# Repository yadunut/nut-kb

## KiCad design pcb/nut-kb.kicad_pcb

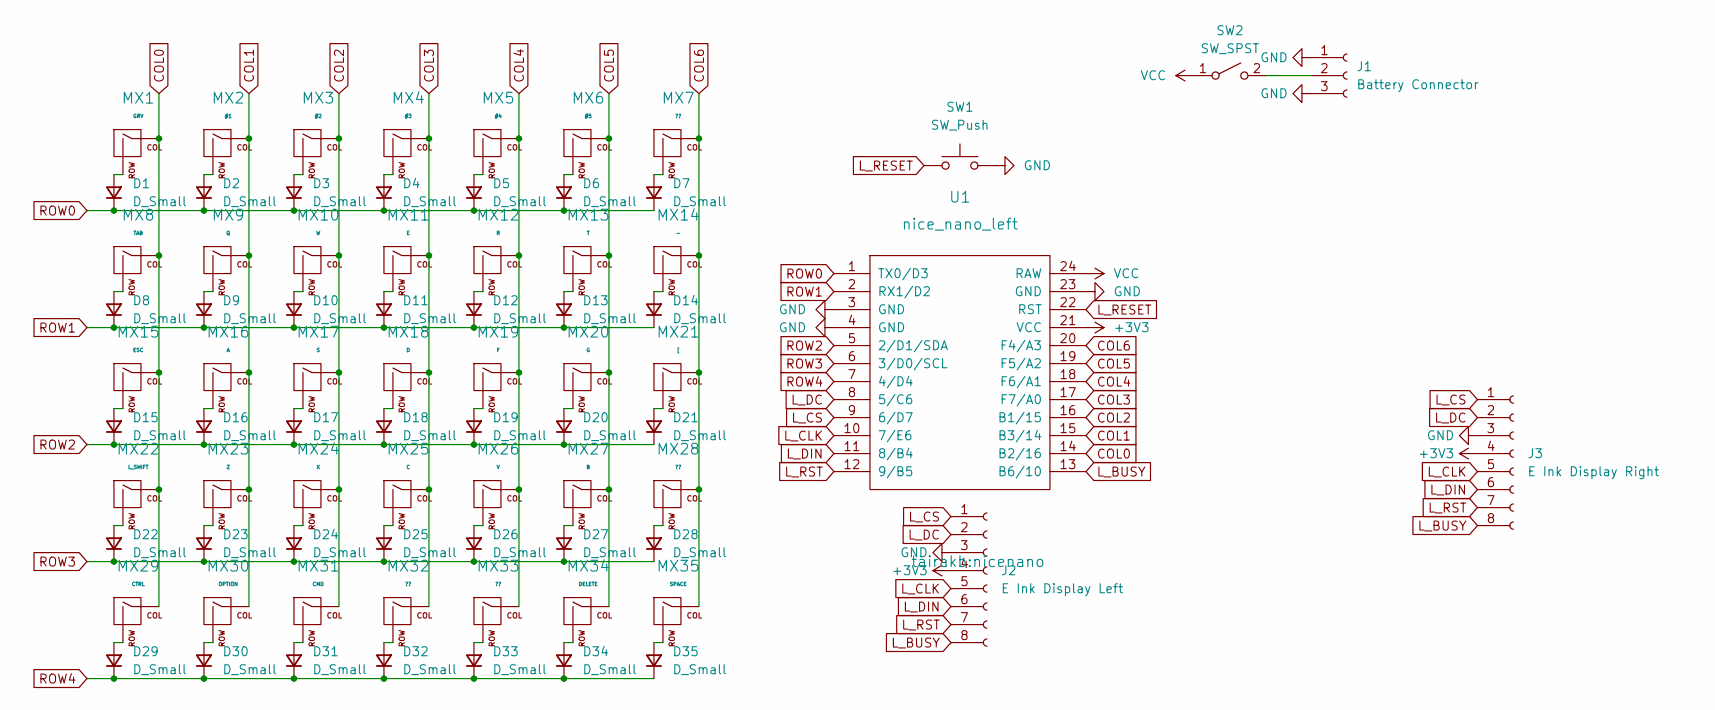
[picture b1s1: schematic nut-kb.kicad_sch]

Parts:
D1, D2, D3, D4, D5, D6, D7, D8, D9, D10, D11, D12, D13, D14, D15, D16, D17, D18, D19, D20, D21, D22, D23, D24, D25, D26, D27, D28, D29, D30, D31, D32, D33, D34, D35: D_Small; D_SOD-123
J1: Battery Connector; JST_PH_B3B-PH-K_1x03_P2.00mm_Vertical
J2: E Ink Display Left; PinSocket_1x08_P2.54mm_Vertical
J3: E Ink Display Right; PinSocket_1x08_P2.54mm_Vertical
MX1: GRV; SW_PG1350_reversible
MX2: #1; SW_PG1350_reversible
MX3: #2; SW_PG1350_reversible
MX4: #3; SW_PG1350_reversible
MX5: #4; SW_PG1350_reversible
MX6: #5; SW_PG1350_reversible
MX7, MX28, MX32, MX33: ??; SW_PG1350_reversible
MX8: TAB; SW_PG1350_reversible
MX9: Q; SW_PG1350_reversible
MX10: W; SW_PG1350_reversible
MX11: E; SW_PG1350_reversible
MX12: R; SW_PG1350_reversible
MX13: T; SW_PG1350_reversible
MX14: -; SW_PG1350_reversible
MX15: ESC; SW_PG1350_reversible
MX16: A; SW_PG1350_reversible
MX17: S; SW_PG1350_reversible
MX18: D; SW_PG1350_reversible
MX19: F; SW_PG1350_reversible
MX20: G; SW_PG1350_reversible
MX21: [; SW_PG1350_reversible
MX22: L_SHIFT; SW_PG1350_reversible
MX23: Z; SW_PG1350_reversible
MX24: X; SW_PG1350_reversible
MX25: C; SW_PG1350_reversible
MX26: V; SW_PG1350_reversible
MX27: B; SW_PG1350_reversible
MX29: CTRL; SW_PG1350_reversible
MX30: OPTION; SW_PG1350_reversible
MX31: CMD; SW_PG1350_reversible
MX34: DELETE; SW_PG1350_reversible
MX35: SPACE; SW_PG1350_reversible
SW1: SW_Push; SW_PUSH_6mm
SW2: SW_SPST; SW_DIP_SPSTx01_Slide_6.7x4.1mm_W7.62mm_P2.54mm_LowProfile
U1: nice_nano_left; nicenano

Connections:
+3V3: J2.4, J3.4, U1.21 (VCC)
COL0: MX1.1 (COL), MX8.1 (COL), MX15.1 (COL), MX22.1 (COL), MX29.1 (COL), U1.14 (B2/16)
COL1: MX2.1 (COL), MX9.1 (COL), MX16.1 (COL), MX23.1 (COL), MX30.1 (COL), U1.15 (B3/14)
COL2: MX3.1 (COL), MX10.1 (COL), MX17.1 (COL), MX24.1 (COL), MX31.1 (COL), U1.16 (B1/15)
COL3: MX4.1 (COL), MX11.1 (COL), MX18.1 (COL), MX25.1 (COL), MX32.1 (COL), U1.17 (F7/A0)
COL4: MX5.1 (COL), MX12.1 (COL), MX19.1 (COL), MX26.1 (COL), MX33.1 (COL), U1.18 (F6/A1)
COL5: MX6.1 (COL), MX13.1 (COL), MX20.1 (COL), MX27.1 (COL), MX34.1 (COL), U1.19 (F5/A2)
COL6: MX7.1 (COL), MX14.1 (COL), MX21.1 (COL), MX28.1 (COL), MX35.1 (COL), U1.20 (F4/A3)
GND: J1.1, J1.3, J2.3, J3.3, SW1.2, U1.3 (GND), U1.4 (GND), U1.23 (GND)
L_BUSY: J2.8, J3.8, U1.13 (B6/10)
L_CLK: J2.5, J3.5, U1.10 (7/E6)
L_CS: J2.1 (asdf), J3.1 (asdf), U1.9 (6/D7)
L_DC: J2.2, J3.2, U1.8 (5/C6)
L_DIN: J2.6, J3.6, U1.11 (8/B4)
L_RESET: SW1.1, U1.22 (RST)
L_RST: J2.7, J3.7, U1.12 (9/B5)
unnamed: D1.2 (A), MX1.2 (ROW)
unnamed: D2.2 (A), MX2.2 (ROW)
unnamed: D3.2 (A), MX3.2 (ROW)
unnamed: D4.2 (A), MX4.2 (ROW)
unnamed: D5.2 (A), MX5.2 (ROW)
unnamed: D6.2 (A), MX6.2 (ROW)
unnamed: D7.2 (A), MX7.2 (ROW)
unnamed: D8.2 (A), MX8.2 (ROW)
unnamed: D9.2 (A), MX9.2 (ROW)
unnamed: D10.2 (A), MX10.2 (ROW)
unnamed: D11.2 (A), MX11.2 (ROW)
unnamed: D12.2 (A), MX12.2 (ROW)
unnamed: D13.2 (A), MX13.2 (ROW)
unnamed: D14.2 (A), MX14.2 (ROW)
unnamed: D15.2 (A), MX15.2 (ROW)
unnamed: D16.2 (A), MX16.2 (ROW)
unnamed: D17.2 (A), MX17.2 (ROW)
unnamed: D18.2 (A), MX18.2 (ROW)
unnamed: D19.2 (A), MX19.2 (ROW)
unnamed: D20.2 (A), MX20.2 (ROW)
unnamed: D21.2 (A), MX21.2 (ROW)
unnamed: D22.2 (A), MX22.2 (ROW)
unnamed: D23.2 (A), MX23.2 (ROW)
unnamed: D24.2 (A), MX24.2 (ROW)
unnamed: D25.2 (A), MX25.2 (ROW)
unnamed: D26.2 (A), MX26.2 (ROW)
unnamed: D27.2 (A), MX27.2 (ROW)
unnamed: D28.2 (A), MX28.2 (ROW)
unnamed: D29.2 (A), MX29.2 (ROW)
unnamed: D30.2 (A), MX30.2 (ROW)
unnamed: D31.2 (A), MX31.2 (ROW)
unnamed: D32.2 (A), MX32.2 (ROW)
unnamed: D33.2 (A), MX33.2 (ROW)
unnamed: D34.2 (A), MX34.2 (ROW)
unnamed: D35.2 (A), MX35.2 (ROW)
unnamed: J1.2, SW2.2 (B)
ROW0: D1.1 (K), D2.1 (K), D3.1 (K), D4.1 (K), D5.1 (K), D6.1 (K), D7.1 (K), U1.1 (TX0/D3)
ROW1: D8.1 (K), D9.1 (K), D10.1 (K), D11.1 (K), D12.1 (K), D13.1 (K), D14.1 (K), U1.2 (RX1/D2)
ROW2: D15.1 (K), D16.1 (K), D17.1 (K), D18.1 (K), D19.1 (K), D20.1 (K), D21.1 (K), U1.5 (2/D1/SDA)
ROW3: D22.1 (K), D23.1 (K), D24.1 (K), D25.1 (K), D26.1 (K), D27.1 (K), D28.1 (K), U1.6 (3/D0/SCL)
ROW4: D29.1 (K), D30.1 (K), D31.1 (K), D32.1 (K), D33.1 (K), D34.1 (K), D35.1 (K), U1.7 (4/D4)
VCC: SW2.1 (A), U1.24 (RAW)

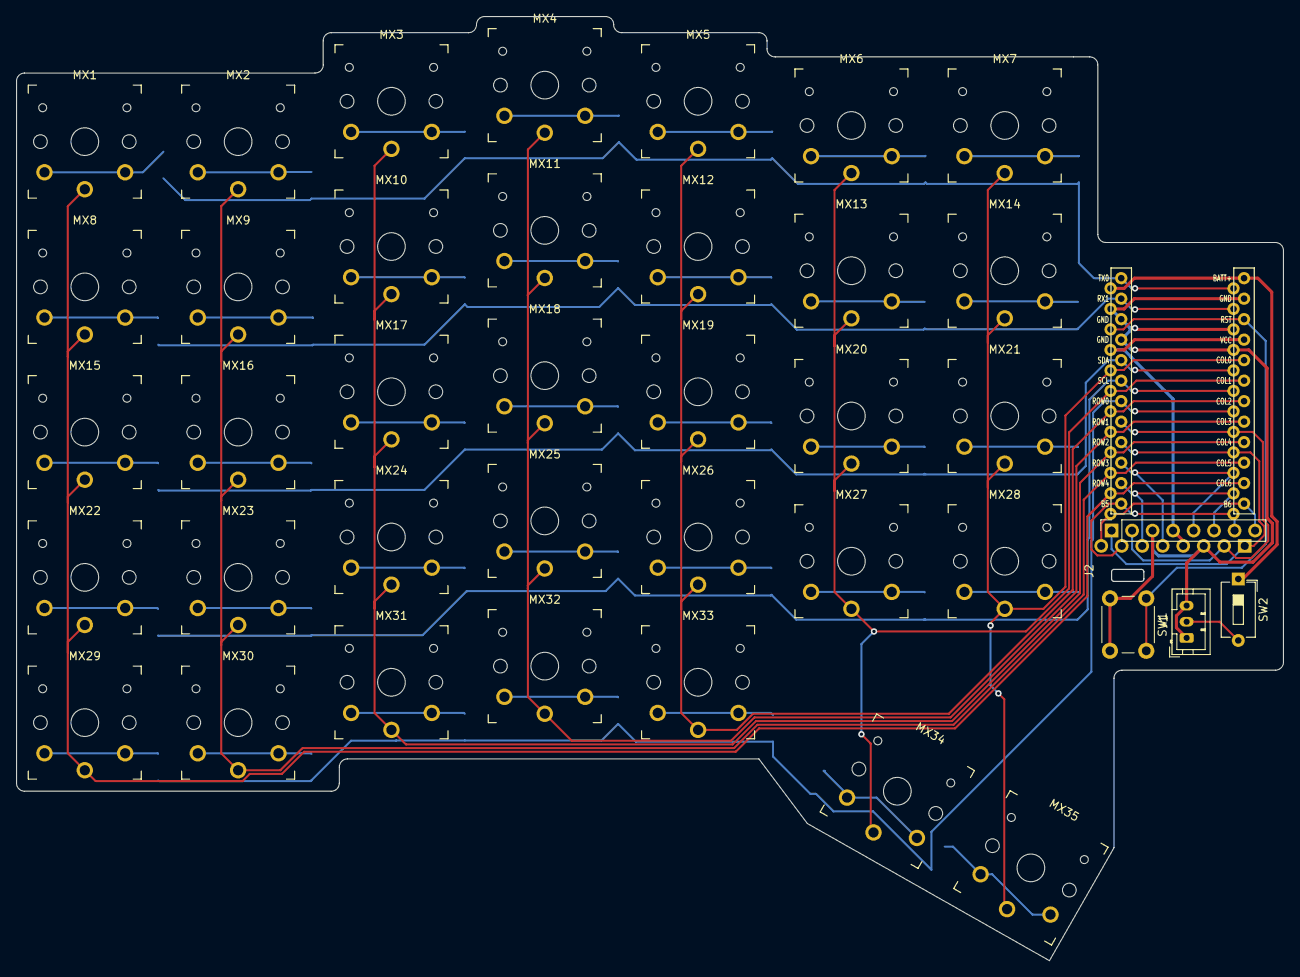
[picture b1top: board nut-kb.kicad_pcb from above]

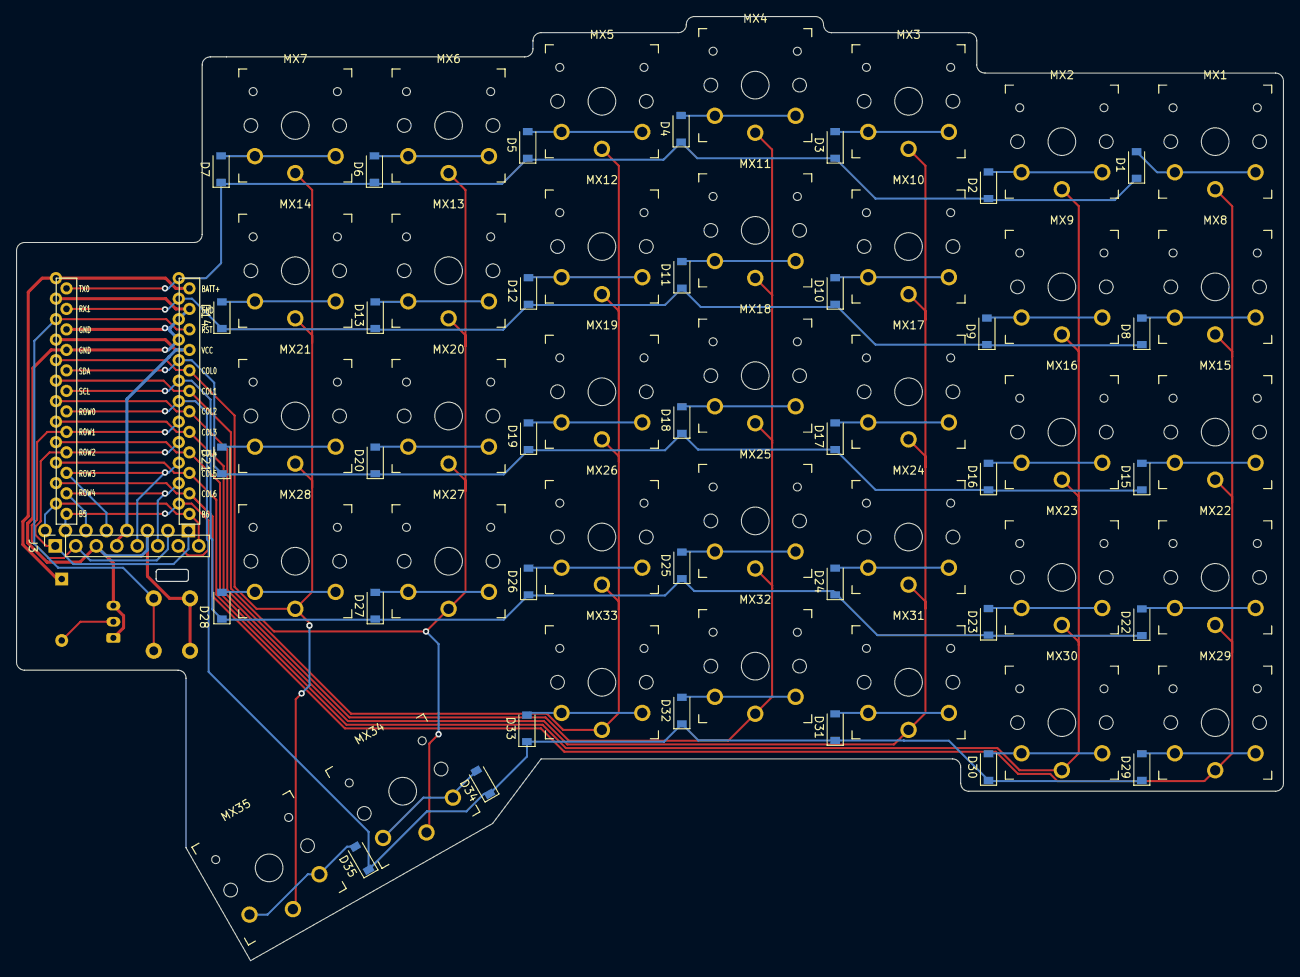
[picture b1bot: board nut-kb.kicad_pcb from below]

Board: 2 copper layers, 157.0 x 117.0 mm, 76 parts (36 on the bottom side), 58 nets.

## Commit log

2022-01-31 [pcb] init
2022-01-31 [pcb] add ai03 submodules
2022-01-31 [pcb] add project specific libraries
2022-01-31 [pcb] add schematic
2022-02-13 [pcb] finish everything for MX
2022-02-21 [pcb] choc version done
2022-02-21 [pcb] remove mx/alps
2022-02-27 [pcb] finish keyboard
2022-02-27 [pcb] tairakb

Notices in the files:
parts and their libraries:
Licensed under the MIT License - Copyright (c) 2020 foostan, Based on https://github.com/foostan/kbd/blob/master/kicad-footprints/kbd.pretty/ProMicro_v2.kicad_mod
